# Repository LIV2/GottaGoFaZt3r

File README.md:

# GottaGoFaZt3r Fast RAM

256MB Autoconfig Fast RAM for the Amiga 3000/4000 

## Table of contents
1. [Status](#status)
2. [Features](#features)
3. [Ordering PCBs](#ordering-pcbs)
4. [Bill of materials](#bill-of-materials)
5. [Troubleshooting](#troubleshooting)
6. [Special Thanks and Shoutouts](#special-thanks-and-shoutouts)
7. [License](#license)

## Status
Tested and working in the following configurations:
* Amiga 3000
* Amiga 4000 with A3640

## Features
128MB or 256MB Z3 Fast RAM  
Brand new 32Mx16 SDRAM chips are quite expensive so the board can also be fitted with 16Mx16 chips for a much lower build cost  

## Ordering PCBs
I recommend ordering from JLCPCB as this board was designed within their 4-layer specifications  
Recommended options when ordering:
* Thickness: 1.6mm
* Surface Finish: ENIG-RoHS
* Gold Fingers: Yes
* 45°finger chamfered: Yes

Layer sequence:
|Layer|File|
|-|-|
|L1|GottaGoFaSDZ3-F_Cu.gbr|
|L2|GottaGoFaSDZ3-In1_Cu.gbr|
|L3|GottaGoFaSDZ3-In2_Cu.gbr|
|L4|GottaGoFaSDZ3-B_Cu.gbr|

## Bill of materials

|Component|Location|QTY|Link|Notes|
|---------|--------|---|----|-----|
|0.1uF Ceramic Capacitor, 0603|C4-15,C17-44|40|[Mouser](https://www.mouser.com/ProductDetail/80-C603C104K5RAC3121)<br />[DigiKey](https://www.digikey.com/short/f7trtfwt)||
|10uF Ceramic Capacitor, 1206|C2-3,C16|3|[Mouser](https://www.mouser.com/ProductDetail/187-CL31A106MAHNNNE)<br />[DigiKey](https://www.digikey.com/short/rqt1br0q)||
|33 Ohm Resistor, 0603|R1|1|[Mouser](https://www.mouser.com/ProductDetail/603-RT0603DRE0733RL)<br />[DigiKey](https://www.digikey.com/short/40rdd4m1)||
|33 Ohm Resistor network, Convex 1206 (3.2x1.6mm)|RN1-8|8|[Mouser](https://www.mouser.com/ProductDetail/667-EXB-38V330JV)<br />[DigiKey](https://www.digikey.com/short/t08zh4pn)||
|10K Resistor, 0603|R2|1|[Mouser](https://www.mouser.com/ProductDetail/603-RT0603FRD0710KL)<br />[DigiKey](https://www.digikey.com/short/nvvrt5dw)||
|LM1117-3.3 SOT-223|U1|1|[Mouser](https://www.mouser.com/ProductDetail/926-LM1117IMP3.3NOPB)<br />[Digikey](https://www.digikey.se/short/jprv7r4q)||
|74LVC245N TSSOP|U2-5|4|[Mouser](https://www.mouser.com/ProductDetail/595-SN74LVC245APWT)<br />[DigiKey](https://www.digikey.se/short/vbmphn44)|Can be substituted with SN74LVTH245 or SN74LVCR2245|
|AS4C32M16SC 32Mx16 SDRAM, TSSOP-54|U7-10|4|[Mouser](https://www.mouser.com/ProductDetail/913-AS4C32M16SC-7TIN)<br />[DigiKey](https://www.digikey.com/short/wfwn8nmw)|Cheaper option is to use [A3V56S40GTP](https://www.mouser.com/ProductDetail/155-A3V56S40GTP-60) 16Mx16 for a 128MB configuration at a drastically lower price, or scavenge some 32Mx16 SDRAM from old SODIMMs*|
|Xilinx XC95144XL-10TQG100C 10ns 144 Macrocell CPLD|U6|1|[Mouser](https://www.mouser.com/ProductDetail/217-95144XL-10TQ100C)<br />[Digkey](https://www.digikey.com/short/w0r0j288)||
|Clock Oscillator, HCMOS, 7x5mm, 3.3V, ~66MHz|X1|1|[Mouser](https://www.mouser.com/ProductDetail/959-SM7745HEV-66.667)<br />[DigiKey](https://www.digikey.com/short/q8bzfwj4)|Anything close to 66MHz should work<br />Tested at 66.6666MHz|

__*__ I cannot provide technical support for RAM chips other than those explicitly listed in the BOM, others may work but you're on your own

## Troubleshooting
__Problem:__ The board is detected but there is less memory detected than there should be. or you see a message stating that the board is "Defective"  
__Resolution:__
1. Check all soldering looking for bad connections and shorts around the RAM and CPLD
2. Test the RAM using [ATK](https://github.com/keirf/amiga-stuff/releases)  
Look for the relevant region under "List and test regions" and test it  
Consult the memory layout to determine which IC is responsible for any stuck bits you might see

### Memory Layout
The memory is laid out in a way that causes it to wrap around above 128MB when only 128MB of ram is fitted to the card allowing either 128/256MB configuration with the same CPLD firmware.  
Kickstart will notice this wrap and add only 128MB to the free pool in this instance.

|Address|D0-15|D16-31|
|-------|-----|------|
|40000000-43FFFFFF|U9|U7|
|44000000-47FFFFFF|U10|U8|
|48000000-4BFFFFFF|U9|U7|
|4C000000-4FFFFFFF|U10|U8|

## Special Thanks and Shoutouts
* [Niklas Ekström](https://github.com/niklasekstrom) for helping to clean up my messy code
* [GadgetUK164](https://www.youtube.com/gadgetuk164) for ~~being a guinea pig~~ beta testing many of my boards
* SparxUK also for being a helpful beta tester of many of my boards
* [CDH](https://github.com/cdhooper) and [Stefan Reinauer](https://github.com/reinauer) for helping me to get my A3000 going 
* [Rob "peepo" Taylor](https://tindie.com/stores/bobsbits/) whose A500++ got me started on my journey of tinkering with Amigas
* [jbilander](https://github.com/jbilander) who came up with the cool name :)
* RetroFletch
* [SukkoPera](https://github.com/SukkoPera)

## License

[![CC BY-SA 4.0][cc-by-sa-shield]][cc-by-sa]

This work is licensed under a
[Creative Commons Attribution-ShareAlike 4.0 International License][cc-by-sa].

[![CC BY-SA 4.0][cc-by-sa-image]][cc-by-sa]

[cc-by-sa]: http://creativecommons.org/licenses/by-sa/4.0/
[cc-by-sa-image]: https://licensebuttons.net/l/by-sa/4.0/88x31.png
[cc-by-sa-shield]: https://img.shields.io/badge/License-CC%20BY--SA%204.0-lightgrey.svg

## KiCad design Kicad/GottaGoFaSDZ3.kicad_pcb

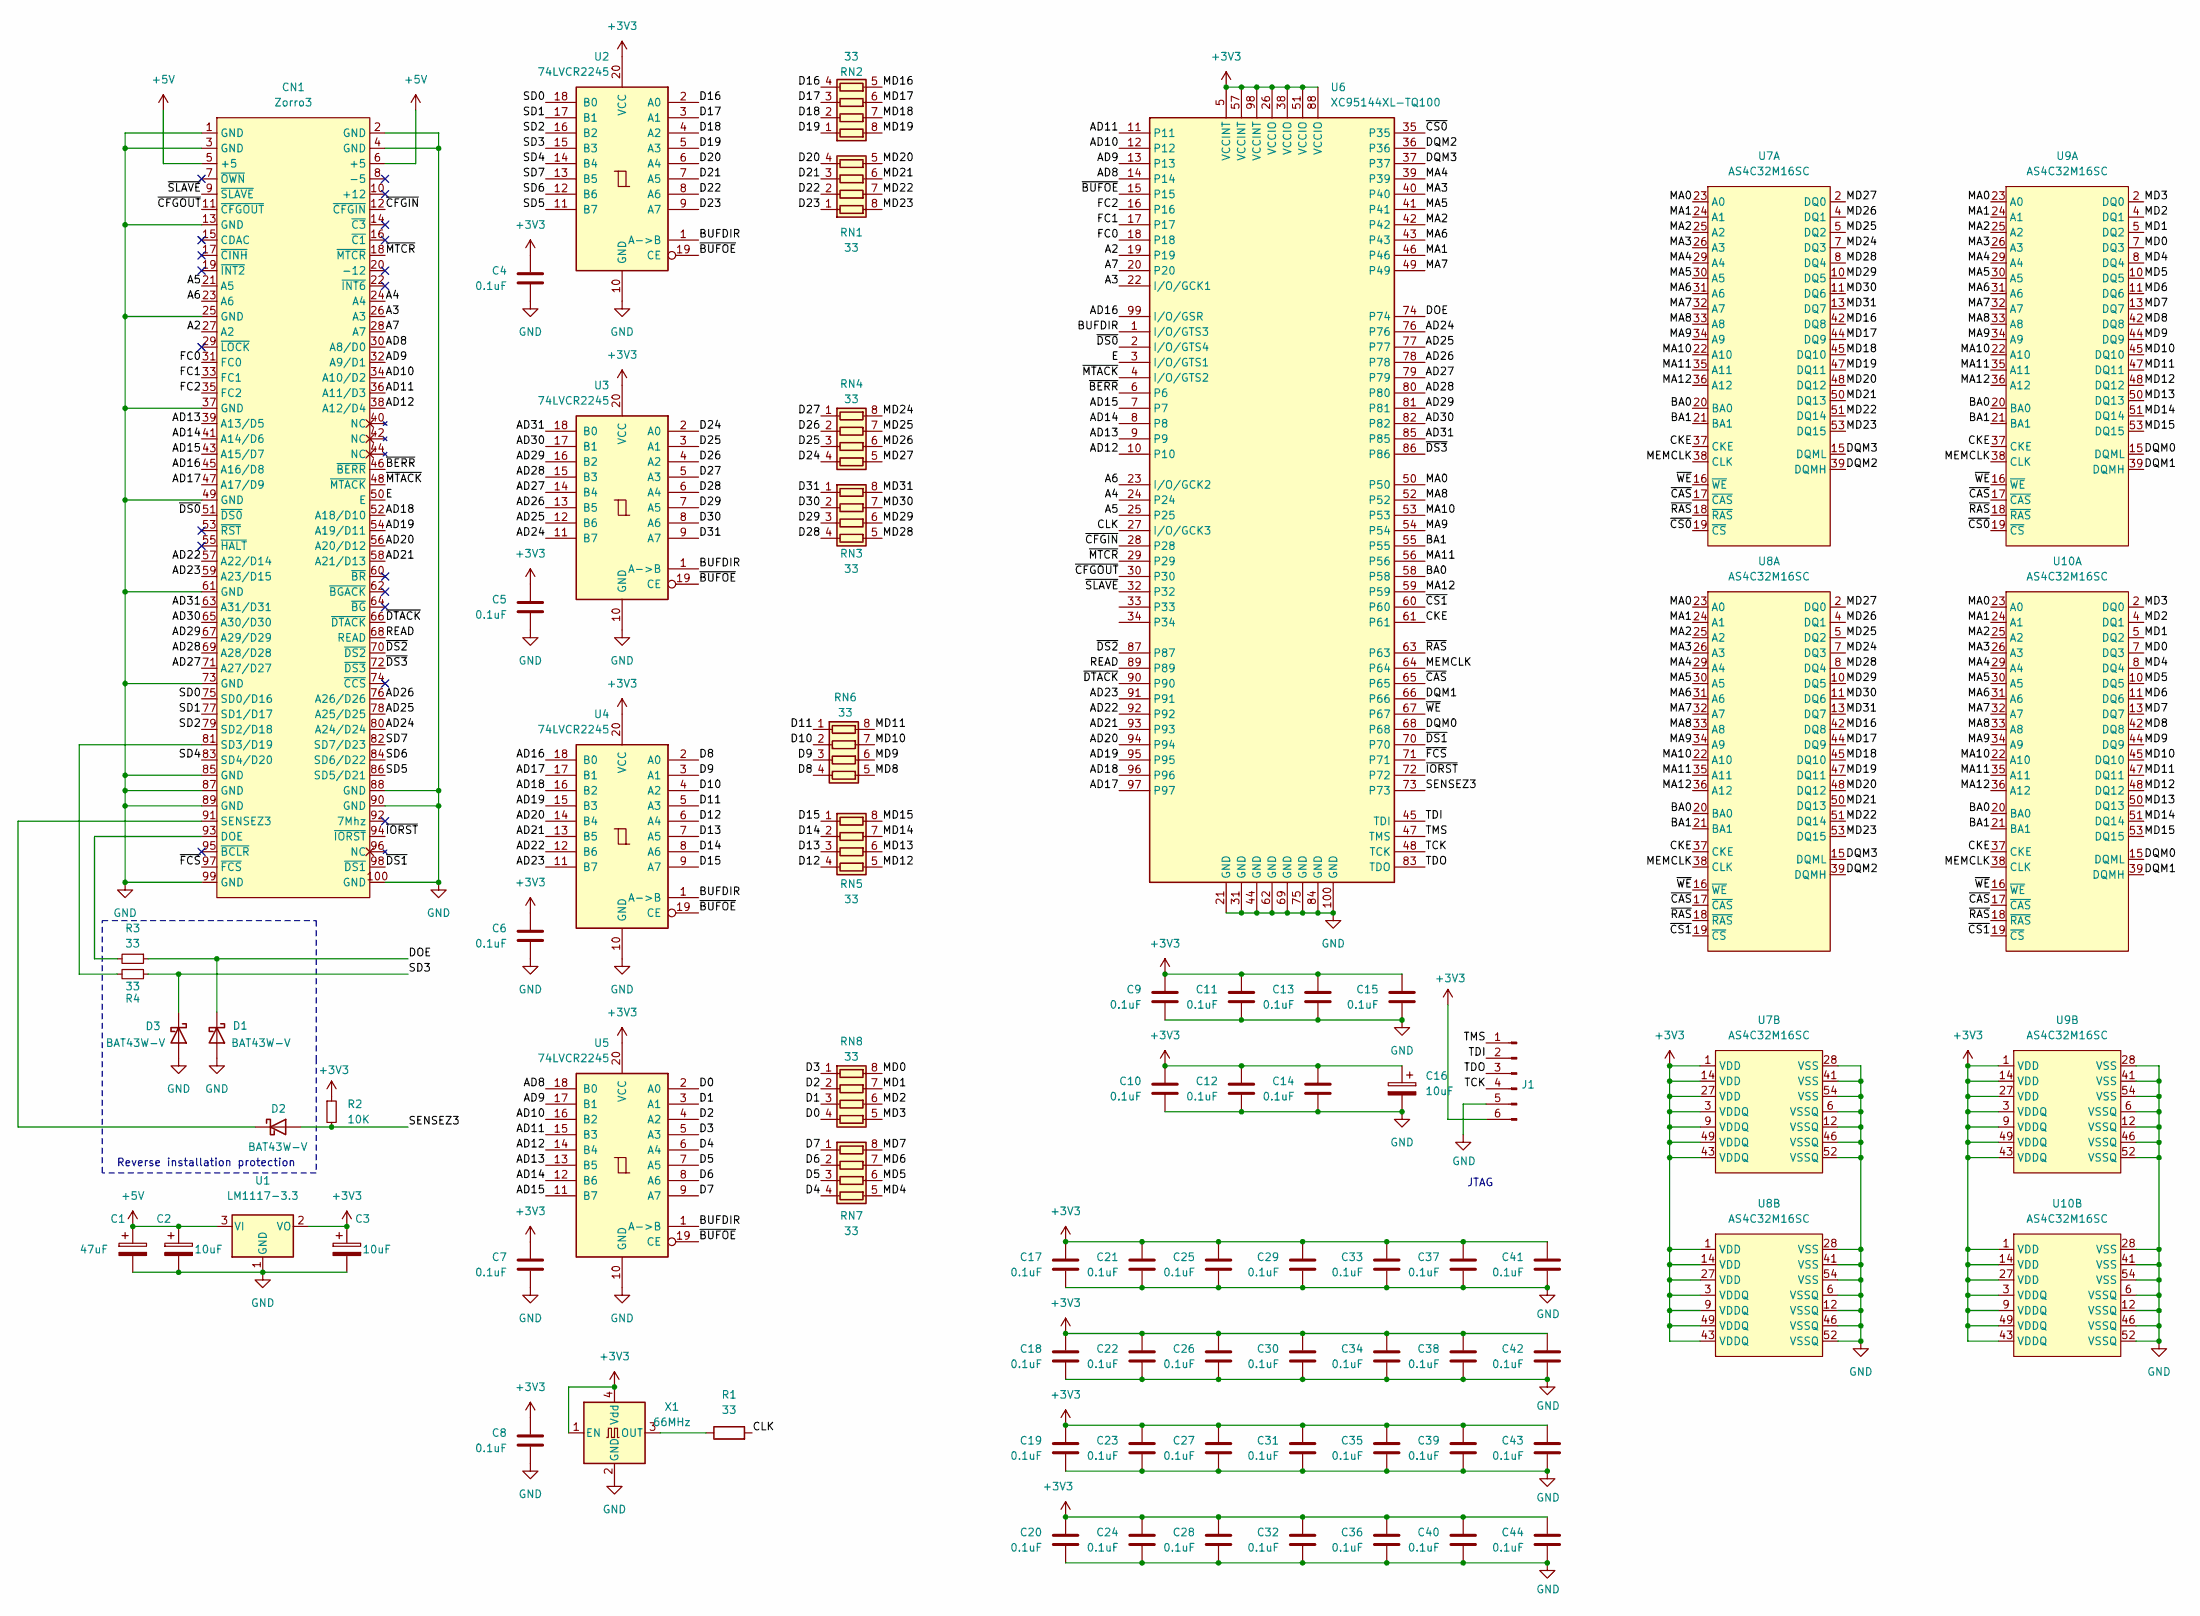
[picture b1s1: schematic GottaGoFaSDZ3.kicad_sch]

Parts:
C1: 47uF; CP_Radial_D6.3mm_P2.50mm; Mouser # 667-ECE-A1CKA101; LCSC # C239310
C2, C3, C16: 10uF; C_1206_3216Metric_Pad1.33x1.80mm_HandSolder; Mouser # 80-T491A106M020
C4: 0.1uF; C_0603_1608Metric_Pad1.08x0.95mm_HandSolder; Mouser # 80-C603C104K5RAC3121; LCSC # C14663
C5, C6, C7, C8, C9, C10, C11, C12, C13, C14, C15, C17, C18, C19, C20, C21, C22, C23, C24, C25, C26, C27, C28, C29, C30, C31, C32, C33, C34, C35, C36, C37, C38, C39, C40, C41, C42, C43, C44: 0.1uF; C_0603_1608Metric_Pad1.08x0.95mm_HandSolder; Mouser # 80-C603C104K5RAC3121
CN1: Zorro3
D1, D2, D3: BAT43W-V; D_SOD-123; Mouser # 78-BAT43W-G3-18; LCSC # C7502694
J1: Conn_01x06_Male; PinHeader_1x06_P2.54mm_Vertical
R1: 33; R_0603_1608Metric_Pad0.98x0.95mm_HandSolder; Mouser # 279-CRG0603F33R; LCSC # C23140
R2: 10K; R_0603_1608Metric_Pad0.98x0.95mm_HandSolder; Mouser # 279-CRGH0603J10K; LCSC # C25804
R3, R4: 33; R_0805_2012Metric_Pad1.20x1.40mm_HandSolder; Mouser # 279-CRG0603F33R; LCSC # C23140
RN1, RN2, RN3, RN4, RN5, RN6, RN7, RN8: 33; R_Array_Convex_4x0603; Mouser # 603-YC164-FR-0733RL; LCSC # C25508
U1: LM1117-3.3; SOT-223-3_TabPin2; Mouser # 926-LM1117IMP3.3NOPB
U2, U3, U4, U5: 74LVCR2245; TSSOP-20_4.4x6.5mm_P0.65mm; Mouser # 595-SN74LVC245APWT
U6: XC95144XL-TQ100; TQFP-100_14x14mm_P0.5mm; Mouser # 217-5144XL-10TQG100C; LCSC # C45126
U7, U8, U9, U10: AS4C32M16SC; TSOP-II-54_22.2x10.16mm_P0.8mm
X1: 66MHz; Oscillator_SMD_Abracon_ASV-4Pin_7.0x5.1mm_HandSoldering; Mouser # 959-SM7745HEV-66.667; LCSC # C387152

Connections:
+3V3: C3.1, C4.1, C5.1, C6.1, C7.1, C8.1, C9.1, C10.1, C11.1, C12.1, C13.1, C14.1, C15.1, C16.1, C17.1, C18.1, C19.1, C20.1, C21.1, C22.1, C23.1, C24.1, C25.1, C26.1, C27.1, C28.1, C29.1, C30.1, C31.1, C32.1, C33.1, C34.1, C35.1, C36.1, C37.1, C38.1, C39.1, C40.1, C41.1, C42.1, C43.1, C44.1, J1.6, R2.1, U1.2 (VO), U2.20 (VCC), U3.20 (VCC), U4.20 (VCC), U5.20 (VCC), U6.5 (VCCINT), U6.26 (VCCIO), U6.38 (VCCIO), U6.51 (VCCIO), U6.57 (VCCINT), U6.88 (VCCIO), U6.98 (VCCINT), U7.1 (VDD), U7.3 (VDDQ), U7.9 (VDDQ), U7.14 (VDD), U7.27 (VDD), U7.43 (VDDQ), U7.49 (VDDQ), U8.1 (VDD), U8.3 (VDDQ), U8.9 (VDDQ), U8.14 (VDD), U8.27 (VDD), U8.43 (VDDQ), U8.49 (VDDQ), U9.1 (VDD), U9.3 (VDDQ), U9.9 (VDDQ), U9.14 (VDD), U9.27 (VDD), U9.43 (VDDQ), U9.49 (VDDQ), U10.1 (VDD), U10.3 (VDDQ), U10.9 (VDDQ), U10.14 (VDD), U10.27 (VDD), U10.43 (VDDQ), U10.49 (VDDQ), X1.1 (EN), X1.4 (Vdd)
+5V: C1.1, C2.1, CN1.5 (+5), CN1.6 (+5), U1.3 (VI)
/A2: CN1.27 (A2), U6.19
/A3: CN1.26 (A3), U6.22 (I/O/GCK1)
/A4: CN1.24 (A4), U6.24
/A5: CN1.21 (A5), U6.25
/A6: CN1.23 (A6), U6.23 (I/O/GCK2)
/A7: CN1.28 (A7), U6.20
/AD8: CN1.30 (A8/D0), U5.18 (B0), U6.14
/AD9: CN1.32 (A9/D1), U5.17 (B1), U6.13
/AD10: CN1.34 (A10/D2), U5.16 (B2), U6.12
/AD11: CN1.36 (A11/D3), U5.15 (B3), U6.11
/AD12: CN1.38 (A12/D4), U5.14 (B4), U6.10
/AD13: CN1.39 (A13/D5), U5.13 (B5), U6.9
/AD14: CN1.41 (A14/D6), U5.12 (B6), U6.8
/AD15: CN1.43 (A15/D7), U5.11 (B7), U6.7
/AD16: CN1.45 (A16/D8), U4.18 (B0), U6.99 (I/O/GSR)
/AD17: CN1.47 (A17/D9), U4.17 (B1), U6.97
/AD18: CN1.52 (A18/D10), U4.16 (B2), U6.96
/AD19: CN1.54 (A19/D11), U4.15 (B3), U6.95
/AD20: CN1.56 (A20/D12), U4.14 (B4), U6.94
/AD21: CN1.58 (A21/D13), U4.13 (B5), U6.93
/AD22: CN1.57 (A22/D14), U4.12 (B6), U6.92
/AD23: CN1.59 (A23/D15), U4.11 (B7), U6.91
/AD24: CN1.80 (A24/D24), U3.11 (B7), U6.76
/AD25: CN1.78 (A25/D25), U3.12 (B6), U6.77
/AD26: CN1.76 (A26/D26), U3.13 (B5), U6.78
/AD27: CN1.71 (A27/D27), U3.14 (B4), U6.79
/AD28: CN1.69 (A28/D28), U3.15 (B3), U6.80
/AD29: CN1.67 (A29/D29), U3.16 (B2), U6.81
/AD30: CN1.65 (A30/D30), U3.17 (B1), U6.82
/AD31: CN1.63 (A31/D31), U3.18 (B0), U6.85
/BA0: U6.58, U7.20 (BA0), U8.20 (BA0), U9.20 (BA0), U10.20 (BA0)
/BA1: U6.55, U7.21 (BA1), U8.21 (BA1), U9.21 (BA1), U10.21 (BA1)
/BUFDIR: U2.1 (A->B), U3.1 (A->B), U4.1 (A->B), U5.1 (A->B), U6.1 (I/O/GTS3)
/CKE: U6.61, U7.37 (CKE), U8.37 (CKE), U9.37 (CKE), U10.37 (CKE)
/CLK: R1.2, U6.27 (I/O/GCK3)
/D0: RN8.4 (R4.1), U5.2 (A0)
/D1: RN8.3 (R3.1), U5.3 (A1)
/D2: RN8.2 (R2.1), U5.4 (A2)
/D3: RN8.1 (R1.1), U5.5 (A3)
/D4: RN7.4 (R4.1), U5.6 (A4)
/D5: RN7.3 (R3.1), U5.7 (A5)
/D6: RN7.2 (R2.1), U5.8 (A6)
/D7: RN7.1 (R1.1), U5.9 (A7)
/D8: RN6.4 (R4.1), U4.2 (A0)
/D9: RN6.3 (R3.1), U4.3 (A1)
/D10: RN6.2 (R2.1), U4.4 (A2)
/D11: RN6.1 (R1.1), U4.5 (A3)
/D12: RN5.4 (R4.1), U4.6 (A4)
/D13: RN5.3 (R3.1), U4.7 (A5)
/D14: RN5.2 (R2.1), U4.8 (A6)
/D15: RN5.1 (R1.1), U4.9 (A7)
/D16: RN2.4 (R4.1), U2.2 (A0)
/D17: RN2.3 (R3.1), U2.3 (A1)
/D18: RN2.2 (R2.1), U2.4 (A2)
/D19: RN2.1 (R1.1), U2.5 (A3)
/D20: RN1.4 (R4.1), U2.6 (A4)
/D21: RN1.3 (R3.1), U2.7 (A5)
/D22: RN1.2 (R2.1), U2.8 (A6)
/D23: RN1.1 (R1.1), U2.9 (A7)
/D24: RN4.4 (R4.1), U3.2 (A0)
/D25: RN4.3 (R3.1), U3.3 (A1)
/D26: RN4.2 (R2.1), U3.4 (A2)
/D27: RN4.1 (R1.1), U3.5 (A3)
/D28: RN3.4 (R4.1), U3.6 (A4)
/D29: RN3.3 (R3.1), U3.7 (A5)
/D30: RN3.2 (R2.1), U3.8 (A6)
/D31: RN3.1 (R1.1), U3.9 (A7)
/DOE: D1.1 (K), R3.1, U6.74
/DQM0: U6.68, U9.15 (DQML), U10.15 (DQML)
/DQM1: U6.66, U9.39 (DQMH), U10.39 (DQMH)
/DQM2: U6.36, U7.39 (DQMH), U8.39 (DQMH)
/DQM3: U6.37, U7.15 (DQML), U8.15 (DQML)
/E: CN1.50 (E), U6.3 (I/O/GTS1)
/FC0: CN1.31 (FC0), U6.18
/FC1: CN1.33 (FC1), U6.17
/FC2: CN1.35 (FC2), U6.16
/MA0: U6.50, U7.23 (A0), U8.23 (A0), U9.23 (A0), U10.23 (A0)
/MA1: U6.46, U7.24 (A1), U8.24 (A1), U9.24 (A1), U10.24 (A1)
/MA2: U6.42, U7.25 (A2), U8.25 (A2), U9.25 (A2), U10.25 (A2)
/MA3: U6.40, U7.26 (A3), U8.26 (A3), U9.26 (A3), U10.26 (A3)
/MA4: U6.39, U7.29 (A4), U8.29 (A4), U9.29 (A4), U10.29 (A4)
/MA5: U6.41, U7.30 (A5), U8.30 (A5), U9.30 (A5), U10.30 (A5)
/MA6: U6.43, U7.31 (A6), U8.31 (A6), U9.31 (A6), U10.31 (A6)
/MA7: U6.49, U7.32 (A7), U8.32 (A7), U9.32 (A7), U10.32 (A7)
/MA8: U6.52, U7.33 (A8), U8.33 (A8), U9.33 (A8), U10.33 (A8)
/MA9: U6.54, U7.34 (A9), U8.34 (A9), U9.34 (A9), U10.34 (A9)
/MA10: U6.53, U7.22 (A10), U8.22 (A10), U9.22 (A10), U10.22 (A10)
/MA11: U6.56, U7.35 (A11), U8.35 (A11), U9.35 (A11), U10.35 (A11)
/MA12: U6.59, U7.36 (A12), U8.36 (A12), U9.36 (A12), U10.36 (A12)
/MD0: RN8.8 (R1.2), U9.7 (DQ3), U10.7 (DQ3)
/MD1: RN8.7 (R2.2), U9.5 (DQ2), U10.5 (DQ2)
/MD2: RN8.6 (R3.2), U9.4 (DQ1), U10.4 (DQ1)
/MD3: RN8.5 (R4.2), U9.2 (DQ0), U10.2 (DQ0)
/MD4: RN7.5 (R4.2), U9.8 (DQ4), U10.8 (DQ4)
/MD5: RN7.6 (R3.2), U9.10 (DQ5), U10.10 (DQ5)
/MD6: RN7.7 (R2.2), U9.11 (DQ6), U10.11 (DQ6)
/MD7: RN7.8 (R1.2), U9.13 (DQ7), U10.13 (DQ7)
/MD8: RN6.5 (R4.2), U9.42 (DQ8), U10.42 (DQ8)
/MD9: RN6.6 (R3.2), U9.44 (DQ9), U10.44 (DQ9)
/MD10: RN6.7 (R2.2), U9.45 (DQ10), U10.45 (DQ10)
/MD11: RN6.8 (R1.2), U9.47 (DQ11), U10.47 (DQ11)
/MD12: RN5.5 (R4.2), U9.48 (DQ12), U10.48 (DQ12)
/MD13: RN5.6 (R3.2), U9.50 (DQ13), U10.50 (DQ13)
/MD14: RN5.7 (R2.2), U9.51 (DQ14), U10.51 (DQ14)
/MD15: RN5.8 (R1.2), U9.53 (DQ15), U10.53 (DQ15)
/MD16: RN2.5 (R4.2), U7.42 (DQ8), U8.42 (DQ8)
/MD17: RN2.6 (R3.2), U7.44 (DQ9), U8.44 (DQ9)
/MD18: RN2.7 (R2.2), U7.45 (DQ10), U8.45 (DQ10)
/MD19: RN2.8 (R1.2), U7.47 (DQ11), U8.47 (DQ11)
/MD20: RN1.5 (R4.2), U7.48 (DQ12), U8.48 (DQ12)
/MD21: RN1.6 (R3.2), U7.50 (DQ13), U8.50 (DQ13)
/MD22: RN1.7 (R2.2), U7.51 (DQ14), U8.51 (DQ14)
/MD23: RN1.8 (R1.2), U7.53 (DQ15), U8.53 (DQ15)
/MD24: RN4.8 (R1.2), U7.7 (DQ3), U8.7 (DQ3)
/MD25: RN4.7 (R2.2), U7.5 (DQ2), U8.5 (DQ2)
/MD26: RN4.6 (R3.2), U7.4 (DQ1), U8.4 (DQ1)
/MD27: RN4.5 (R4.2), U7.2 (DQ0), U8.2 (DQ0)
/MD28: RN3.5 (R4.2), U7.8 (DQ4), U8.8 (DQ4)
/MD29: RN3.6 (R3.2), U7.10 (DQ5), U8.10 (DQ5)
/MD30: RN3.7 (R2.2), U7.11 (DQ6), U8.11 (DQ6)
/MD31: RN3.8 (R1.2), U7.13 (DQ7), U8.13 (DQ7)
/MEMCLK: U6.64, U7.38 (CLK), U8.38 (CLK), U9.38 (CLK), U10.38 (CLK)
/READ: CN1.68 (READ), U6.89
/SD0: CN1.75 (SD0/D16), U2.18 (B0)
/SD1: CN1.77 (SD1/D17), U2.17 (B1)
/SD2: CN1.79 (SD2/D18), U2.16 (B2)
/SD3: D3.1 (K), R4.1, U2.15 (B3)
/SD4: CN1.83 (SD4/D20), U2.14 (B4)
/SD5: CN1.86 (SD5/D21), U2.11 (B7)
/SD6: CN1.84 (SD6/D22), U2.12 (B6)
/SD7: CN1.82 (SD7/D23), U2.13 (B5)
/SENSEZ3: D2.2 (A), R2.2, U6.73
/TCK: J1.4, U6.48 (TCK)
/TDI: J1.2, U6.45 (TDI)
/TDO: J1.3, U6.83 (TDO)
/TMS: J1.1, U6.47 (TMS)
/~BERR: CN1.46 (~BERR), U6.6
/~BUFOE: U2.19 (CE), U3.19 (CE), U4.19 (CE), U5.19 (CE), U6.15
/~CAS: U6.65, U7.17 (~CAS), U8.17 (~CAS), U9.17 (~CAS), U10.17 (~CAS)
/~CFGIN: CN1.12 (~CFGIN), U6.28
/~CFGOUT: CN1.11 (~CFGOUT), U6.30
/~CS0: U6.35, U7.19 (~CS), U9.19 (~CS)
/~CS1: U6.60, U8.19 (~CS), U10.19 (~CS)
/~DS0: CN1.51 (~DS0), U6.2 (I/O/GTS4)
/~DS1: CN1.98 (~DS1), U6.70
/~DS2: CN1.70 (~DS2), U6.87
/~DS3: CN1.72 (~DS3), U6.86
/~DTACK: CN1.66 (~DTACK), U6.90
/~FCS: CN1.97 (~FCS), U6.71
/~IORST: CN1.94 (~IORST), U6.72
/~MTACK: CN1.48 (~MTACK), U6.4 (I/O/GTS2)
/~MTCR: CN1.18 (~MTCR), U6.29
/~RAS: U6.63, U7.18 (~RAS), U8.18 (~RAS), U9.18 (~RAS), U10.18 (~RAS)
/~SLAVE: CN1.9 (~SLAVE), U6.32
/~WE: U6.67, U7.16 (~WE), U8.16 (~WE), U9.16 (~WE), U10.16 (~WE)
GND: C1.2, C2.2, C3.2, C4.2, C5.2, C6.2, C7.2, C8.2, C9.2, C10.2, C11.2, C12.2, C13.2, C14.2, C15.2, C16.2, C17.2, C18.2, C19.2, C20.2, C21.2, C22.2, C23.2, C24.2, C25.2, C26.2, C27.2, C28.2, C29.2, C30.2, C31.2, C32.2, C33.2, C34.2, C35.2, C36.2, C37.2, C38.2, C39.2, C40.2, C41.2, C42.2, C43.2, C44.2, CN1.1 (GND), CN1.2 (GND), CN1.3 (GND), CN1.4 (GND), CN1.13 (GND), CN1.25 (GND), CN1.37 (GND), CN1.49 (GND), CN1.61 (GND), CN1.73 (GND), CN1.85 (GND), CN1.87 (GND), CN1.88 (GND), CN1.89 (GND), CN1.90 (GND), CN1.99 (GND), CN1.100 (GND), D1.2 (A), D3.2 (A), J1.5, U1.1 (GND), U2.10 (GND), U3.10 (GND), U4.10 (GND), U5.10 (GND), U6.21 (GND), U6.31 (GND), U6.44 (GND), U6.62 (GND), U6.69 (GND), U6.75 (GND), U6.84 (GND), U6.100 (GND), U7.6 (VSSQ), U7.12 (VSSQ), U7.28 (VSS), U7.41 (VSS), U7.46 (VSSQ), U7.52 (VSSQ), U7.54 (VSS), U8.6 (VSSQ), U8.12 (VSSQ), U8.28 (VSS), U8.41 (VSS), U8.46 (VSSQ), U8.52 (VSSQ), U8.54 (VSS), U9.6 (VSSQ), U9.12 (VSSQ), U9.28 (VSS), U9.41 (VSS), U9.46 (VSSQ), U9.52 (VSSQ), U9.54 (VSS), U10.6 (VSSQ), U10.12 (VSSQ), U10.28 (VSS), U10.41 (VSS), U10.46 (VSSQ), U10.52 (VSSQ), U10.54 (VSS), X1.2 (GND)
unnamed: CN1.93 (DOE), R3.2
unnamed: CN1.81 (SD3/D19), R4.2
unnamed: CN1.91 (SENSEZ3), D2.1 (K)
unnamed: R1.1, X1.3 (OUT)

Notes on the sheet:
JTAG
Reverse installation protection

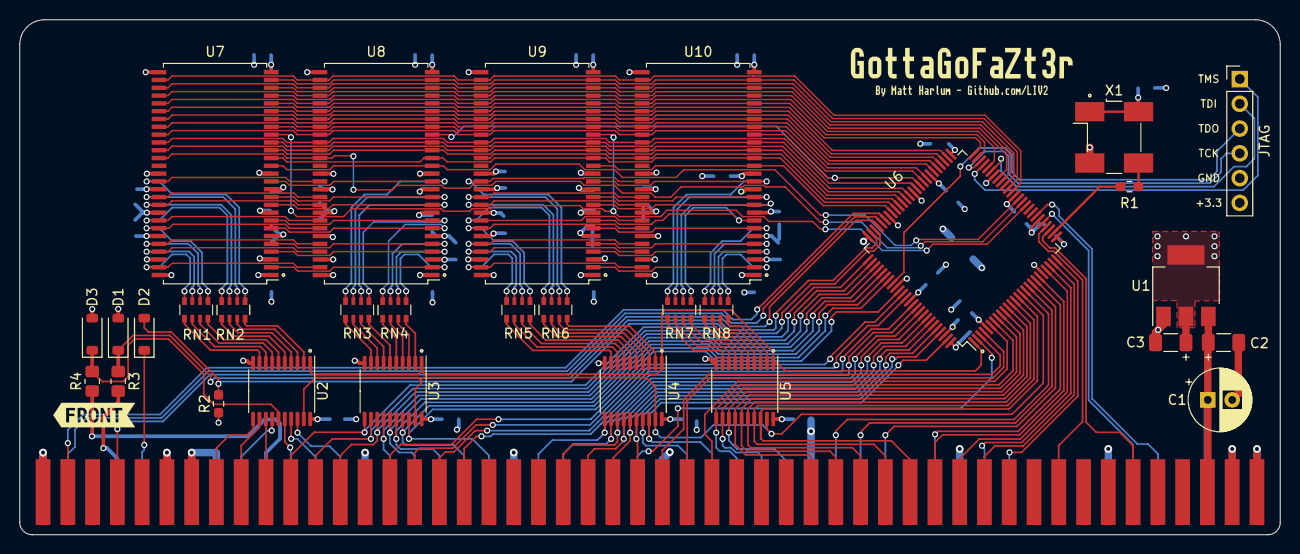
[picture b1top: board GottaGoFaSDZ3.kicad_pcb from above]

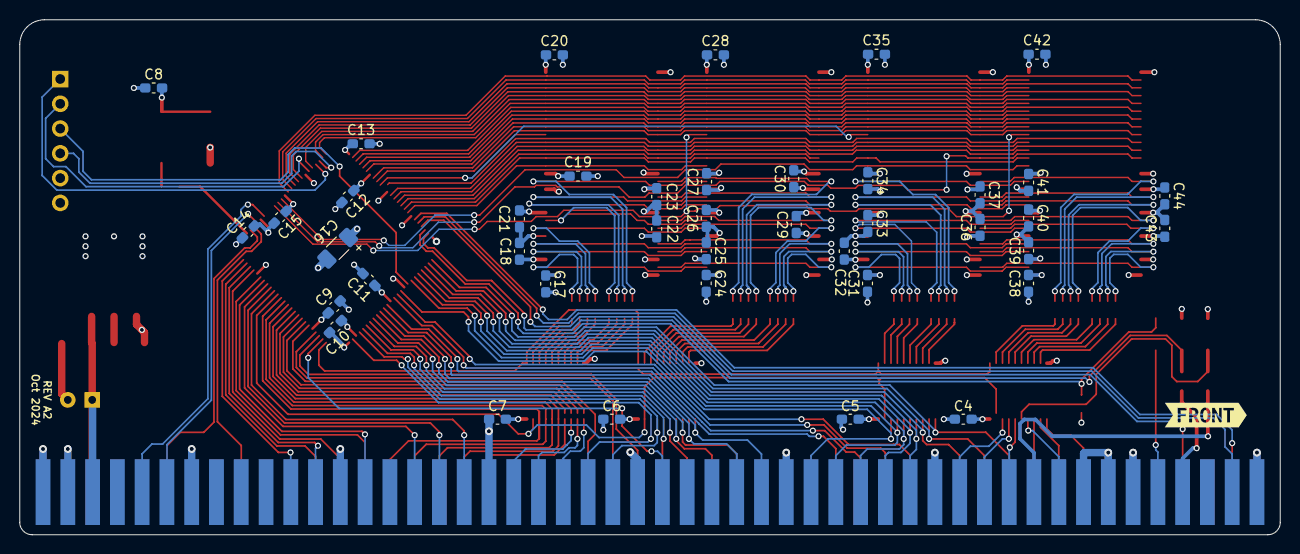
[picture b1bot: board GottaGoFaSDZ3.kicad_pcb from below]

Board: 4 copper layers, 129.2 x 52.8 mm, 76 parts (42 on the bottom side), 162 nets.

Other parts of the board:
kibuzzard-621BB44F: G***; kibuzzard-621BB44F
kibuzzard-621BB463: G***; kibuzzard-621BB463
kibuzzard-622DC477: G***; kibuzzard-622DC477
kibuzzard-622DC493: G***; kibuzzard-622DC493

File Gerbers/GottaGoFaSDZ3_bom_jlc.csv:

"Qty","Comment","Designator","Footprint","LCSC Part #"
"40","0.1uF","C4,C5,C6,C7,C8,C9,C10,C11,C12,C13,C14,C15,C17,C18,C19,C20,C21,C22,C23,C24,C25,C26,C27,C28,C29,C30,C31,C32,C33,C34,C35,C36,C37,C38,C39,C40,C41,C42,C43,C44","C_0603_1608Metric_Pad1.08x0.95mm_HandSolder","C14663"
"3","10uF","C2,C3,C16","C_1206_3216Metric_Pad1.33x1.80mm_HandSolder","C117023"
"1","47uF","C1","CP_Radial_D6.3mm_P2.50mm","C239310"
"3","BAT43W-V","D1,D2,D3","D_SOD-123","C7502694"
"1","33","R1","R_0603_1608Metric_Pad0.98x0.95mm_HandSolder","C23140"
"2","33","R3,R4","R_0805_2012Metric_Pad1.20x1.40mm_HandSolder","C23140"
"1","10K","R2","R_0603_1608Metric_Pad0.98x0.95mm_HandSolder","C25804"
"8","33","RN1,RN2,RN3,RN4,RN5,RN6,RN7,RN8","R_Array_Convex_4x0603","C25508"
"4","74LVCR2245","U2,U3,U4,U5","TSSOP-20_4.4x6.5mm_P0.65mm","C7848"
"4","AS4C32M16SC","U7,U8,U9,U10","TSOP-II-54_22.2x10.16mm_P0.8mm",""
"1","LM1117-3.3","U1","SOT-223-3_TabPin2","C129334"
"1","XC95144XL-TQ100","U6","TQFP-100_14x14mm_P0.5mm","C45126"
"1","66MHz","X1","Oscillator_SMD_Abracon_ASV-4Pin_7.0x5.1mm_HandSoldering","C387152"

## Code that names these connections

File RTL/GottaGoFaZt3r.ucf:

NET "A<2>"    LOC = "P19"  ; 
NET "A<3>"    LOC = "P22"  ; 
NET "A<4>"    LOC = "P24"  ; 
NET "A<5>"    LOC = "P25"  ; 
NET "A<6>"    LOC = "P23"  ; 
NET "A<7>"    LOC = "P20"  ; 
NET "A<10>"  LOC = "P12"  ; 
NET "A<11>"  LOC = "P11"  ; 
NET "A<12>"  LOC = "P10"  ; 
NET "A<13>"  LOC = "P9"  ; 
NET "A<14>"  LOC = "P8"  ; 
NET "A<15>"  LOC = "P7"  ; 
NET "A<16>"  LOC = "P99"  ; 
NET "A<17>"  LOC = "P97"  ; 
NET "A<18>"  LOC = "P96"  ; 
NET "A<19>"  LOC = "P95"  ; 
NET "A<20>"  LOC = "P94"  ; 
NET "A<21>"  LOC = "P93"  ; 
NET "A<22>"  LOC = "P92"  ; 
NET "A<23>"  LOC = "P91"  ; 
NET "A<24>"  LOC = "P76"  ; 
NET "A<25>"  LOC = "P77"  ; 
NET "A<26>"  LOC = "P78"  ; 
NET "A<27>"  LOC = "P79"  ; 
NET "AD<28>"  LOC = "P80"  ; 
NET "AD<29>"  LOC = "P81"  ; 
NET "AD<30>"  LOC = "P82"  ; 
NET "AD<31>"  LOC = "P85"  ; 
NET "A<8>"   LOC = "P14"  ; 
NET "A<9>"   LOC = "P13"  ; 
NET "BA<0>"   LOC = "P58"  ; 
NET "BA<1>"   LOC = "P55"  ; 
NET "BERR_n"   LOC = "P6"  ; 
NET "BUFDIR"  LOC = "P1"  ; 
NET "BUFOE_n"  LOC = "P15"  ; 
NET "CAS_n"    LOC = "P65"  ; 
NET "CFGIN_n"  LOC = "P28"  ; 
NET "CFGOUT_n" LOC = "P30"  ; 
NET "CKE"     LOC = "P61"  ; 
NET "CLK"     LOC = "P27"  ; 
NET "CLK"     BUFG = "CLK" ; 
NET "CS_n<0>"   LOC = "P35"  ; 
NET "CS_n<1>"   LOC = "P60"  ; 
NET "DOE"     LOC = "P74"  ; 
NET "DQM_n<0>"  LOC = "P68"  ; 
NET "DQM_n<1>"  LOC = "P66"  ; 
NET "DQM_n<2>"  LOC = "P36"  ; 
NET "DQM_n<3>"  LOC = "P37"  ; 
NET "DS_n<0>"    LOC = "P2"  ; 
NET "DS_n<1>"    LOC = "P70"  ; 
NET "DS_n<2>"    LOC = "P87"  ; 
NET "DS_n<3>"    LOC = "P86"  ; 
NET "DTACK_n"  LOC = "P90"  ; 
NET "E"       LOC = "P3"  ; 
NET "FC<0>"   LOC = "P18"  ; 
NET "FC<1>"   LOC = "P17"  ; 
NET "FC<2>"   LOC = "P16"  ; 
NET "FCS_n"    LOC = "P71"  ; 
NET "MA<0>"   LOC = "P50"  ; 
NET "MA<1>"   LOC = "P46"  ; 
NET "MA<10>"  LOC = "P53"  ; 
NET "MA<11>"  LOC = "P56"  ; 
NET "MA<12>"  LOC = "P59"  ; 
NET "MA<2>"   LOC = "P42"  ; 
NET "MA<3>"   LOC = "P40"  ; 
NET "MA<4>"   LOC = "P39"  ; 
NET "MA<5>"   LOC = "P41"  ; 
NET "MA<6>"   LOC = "P43"  ; 
NET "MA<7>"   LOC = "P49"  ; 
NET "MA<8>"   LOC = "P52"  ; 
NET "MA<9>"   LOC = "P54"  ; 
NET "MEMCLK"  LOC = "P64"  ; 
NET "MTACK_n"  LOC = "P4"  ; 
NET "MTCR_n"   LOC = "P29"  ; 
NET "RAS_n"    LOC = "P63"  ; 
NET "READ"    LOC = "P89"  ; 
NET "RST_n"    LOC = "P72"  ; 
NET "SENSEZ3" LOC = "P73"  ; 
NET "SLAVE_n"  LOC = "P32"  ; 
NET "TP1"     LOC = "P34"  ; 
NET "TP2"     LOC = "P33"  ; 
NET "WE_n"     LOC = "P67"  ;

NET "CLK" TNM_NET = CLK;
TIMESPEC TS_CLK = PERIOD "CLK" 66 MHz HIGH 50%;

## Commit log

2022-04-23 Tidy up code and add more comments
2022-04-23 Fixup clock enable
2022-04-24 Add RAM datasheet & Zorro III Docs
2022-04-26 Make state machine transitions explicit
2022-05-13 Add License + Documentation
2022-06-07 Remove burst stuff
    Burst feature not working properly and probably not worth the pain
2022-06-07 Add Z3 state machine to autoconfig component
    Previously it just kept writing the base address which caused issues with an A3640/68040 because it would get trashed at the end of the cycle
2022-06-07 Qualify BUFOE_n by FCS_n
2022-06-07 Fixup Autoconfig dtack
    Don't assert DTACK until data time during Autoconfig cycles.
    Asserting on Autoconf address decode was too fast for 68040
2022-06-11 Update Schematic
2022-06-13 Drive RAM and Autoconfig cycles with Z3 State machine
    Previously ram_cycle would latch at FCSn asserted and not be cleared until another FCSn assertion happened
    This caused issues because FCS_n_sync would lead ram_cycle_sync by 1 clock and this caused false memory cycles to start because ram_cycle_sync would still be true when it shouldn't be.
2022-06-20 Minor updates:
    * Set slew rate to slow
    * SDRAM state engine: Don't wait for data strobes on reads
2022-06-20 Update README
    Note that it has been tested on the A4000/040
2022-06-20 README: fix digikey link for resistor networks
2022-06-29 Address matching tweaks
    * Split out ram / autoconf address match
    * Ensure autoconfig cycles don't run unless CFGIN_n is asserted
2022-07-07 Bump DTACK_n up by two clocks bringing it out 30ns sooner
2022-07-10 Public release
    Rev 1A - remove TP1/TP2 and make the board slightly narrower
2022-07-10 README: Fixup digikey link for 74LVC245
2022-07-13 Correct project name in README
2022-07-21 Correct R2 value and memory size in README (thanks to Kavanoz)
2022-08-29 Rewrite ram controller
    Reduce macrocell usage from ~130 to 97
2022-08-31 Makefile tweaks
    * CPLDFIT: set unused outputs (TP1,TP2) to GND
    * Tweak flash target so that it will use the .jed in the Binaries directory
2022-09-30 Fix up LICENSE.md
    This was always meant to be CC-BY-SA but it seems I uploaded the wrong one...
2022-12-28 Add Kibot automation
2023-04-15 Add GitHub release automation
2023-04-15 Switch from Prototype Autoconfig ID to OAHR Manufacturer
2023-04-15 Build firmware
2023-06-28 Remove dirty speed hack
    Previously the board would assert DTACK very early on reads for a speed
    boost...
    This usually isn't a problem because Buster is slow to notice but sometimes causes issues for the A4091
    Thanks goes to dorken @ a1k.org for pointing this out
2023-09-17 README: fixup memory layout table
2024-09-27 Tweak DTACK
    On reads, DTACK will now come out 3 clocks after the READ command to the RAM
    With a CAS latency of 2, the read data will be valid at READ+2
    The A4091 latches data as soon as DTACK is seen, so this delay was needed to make sure the A4091 correctly latches data from GottaGoFaZt3r
2025-02-02 Add reverse install protection
2026-03-18 SDRAM: Row-hit optimization to maximize RAM speed
    Implement open-page / row-hit optimization in the SDRAM controller.
    When consecutive accesses target the same SDRAM row, the controller
    skips the PRECHARGE and ACTIVE phases entirely, saving ~2 CLK cycles
    (~140ns @ 14.3MHz) per access for sequential/localized patterns such
    as memcpy, DMA, stack operations, and framebuffer access.
    Changes:
2026-03-21 Add Verilog regression test suite
2026-03-21 Drop generated test artifacts
2026-03-21 Reduce SDRAM row-hit fit cost
2026-03-21 Fix SDRAM precharge target handling
